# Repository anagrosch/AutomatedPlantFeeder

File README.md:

# AutomatedPlantFeeder (APF)
Custom PCB design to automatically water a house plant.

### Features
The APF implements three sensors described below:

- Water level detection sensor: monitor water level of the water basin

- Soil moisture sensor: monitor moisture level in the soil so that the plant will be watered if the soil becomes too dry.

- Digital humidity/temperature (DHT) sensor: monitor surrounding humidity and temperature

A button and LCD display allow for user interaction with the APF in the following aspects:

- Adjust the watering amount with a button that cycles through three options: low watering, medium watering, and high watering. The options correspond to the length of time that the motorized water pump is turned on for.

- Print the selected water amount value on the LCD when the button is pressed.

- Print the surrounding humidity and temperature, the current water basin's water level status, and the approximate moisture value in the soil on an LCD.

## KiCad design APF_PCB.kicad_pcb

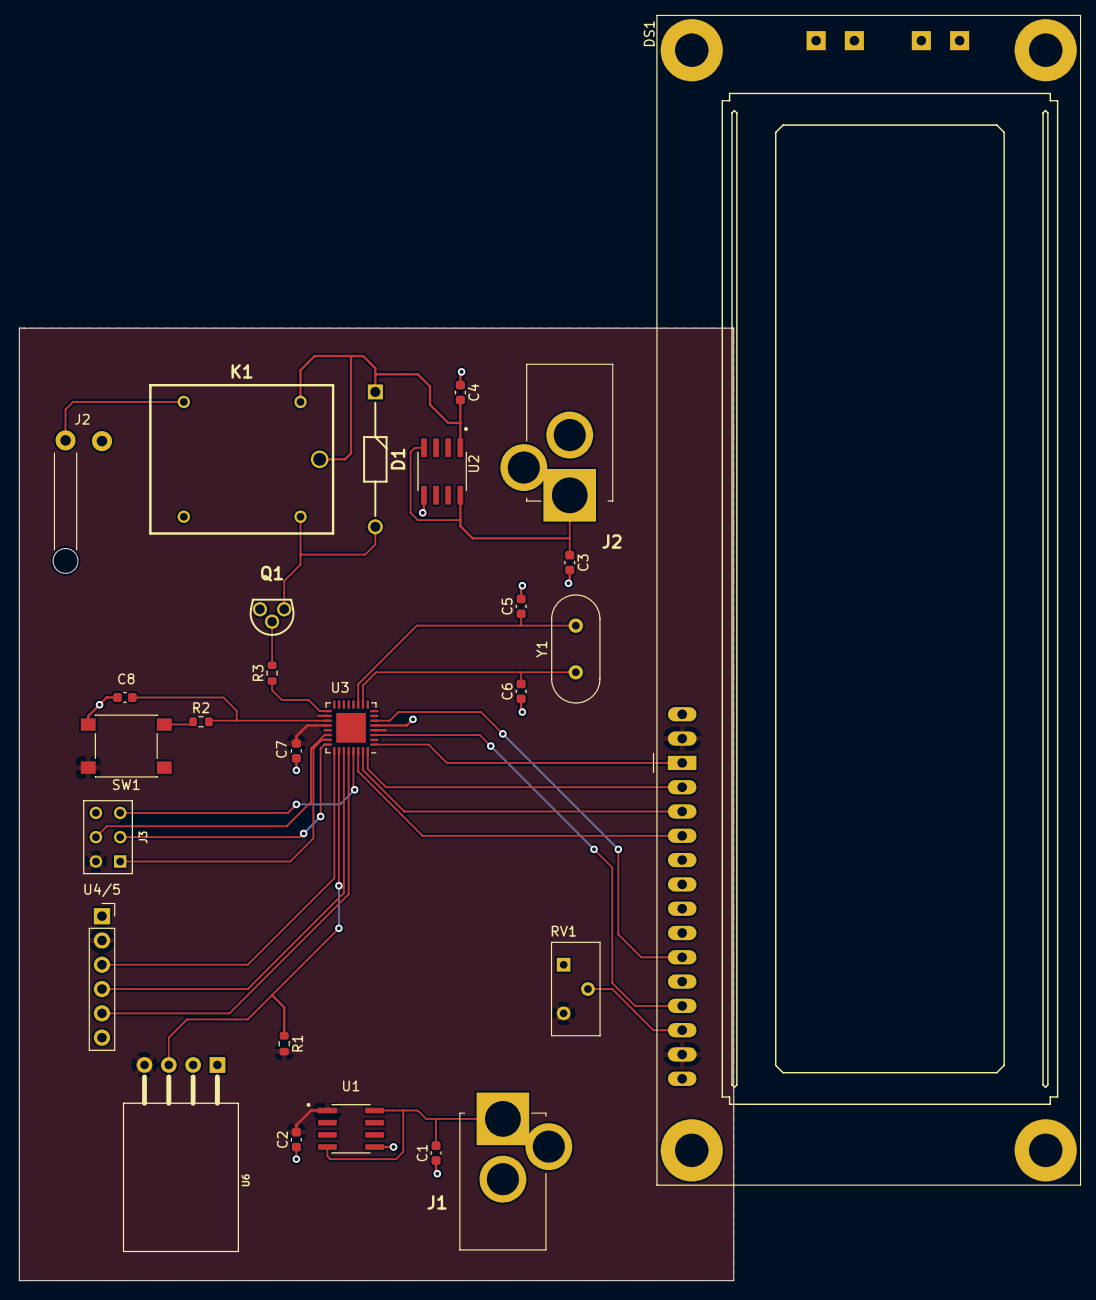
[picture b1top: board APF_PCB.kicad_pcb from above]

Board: 2 copper layers, 74.7 x 99.6 mm, 28 parts (0 on the bottom side), 2 nets.

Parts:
C1, C2, C3, C4, C5, C6, C7, C8: C_0603_1608Metric
D1: DIOAD1405W86L465D235
DS1: LCD-016N002L
J1, J2#3: DCJ25010AK1K
J2: SolderWire-0.5sqmm_1x01_D0.9mm_OD2.1mm
J2#2: SolderWire-0.5sqmm_1x01_D0.9mm_OD2.1mm_Relief
J3: AVR-ISP
K1: SRD
Q1: LM431ACZ
R1, R2, R3: R_0603_1608Metric
RV1: Potentiometer_Bourns_3386X_Horizontal
SW1: SW_Push_1P1T_NO_6x6mm_H9.5mm
U1, U2: SOIC127P600X175-8N
U3: QFN-32-1EP_5x5mm_P0.5mm_EP3.1x3.1mm
U4/5: PinSocket_1x06_P2.54mm_Vertical
U6: SNR4-2.54-15.5X12.0X5.5MM
Y1: Crystal_HC49-U_Vertical

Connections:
+5V1: C2.2, C7.1, DS1.13, DS1.15, J3.VCC, R1.2, RV1.3, SW1.2, U1.1, U3.4, U3.18, U3.20, U4/5.2, U6.4
GND: C1.1, C2.1, C3.2, C4.1, C5.2, C6.1, C7.2, C8.1, DS1.10, DS1.14, DS1.16, J1.2, J2.1, J2#3.2, J3.GND, Q1.3, RV1.1, SW1.1, U1.5, U2.5, U3.5, U4/5.1, U4/5.6, U6.1

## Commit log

2022-12-07 Add Kicad design files
2023-05-12 Update main.c
    utilizing headers
